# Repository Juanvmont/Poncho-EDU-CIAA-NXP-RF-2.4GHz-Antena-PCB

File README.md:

# Poncho-EDU-CIAA-NXP-RF-2.4GHz-Antena-PCB
Este circuito de poncho implementa una unidad de radio que opera en la banda de frecuencias abierta de 2.4GHz y compila con aplicaciones de la EDU-CIAA NXP que soportan el estándar IEEE 802.15.4: IEEE Standards Association. IEEE Standard for Local and metropolitan area networks–Part 15.4: Low-Rate Wireless Personal Area Networks (LR-WPANs) y ZIGBEE.

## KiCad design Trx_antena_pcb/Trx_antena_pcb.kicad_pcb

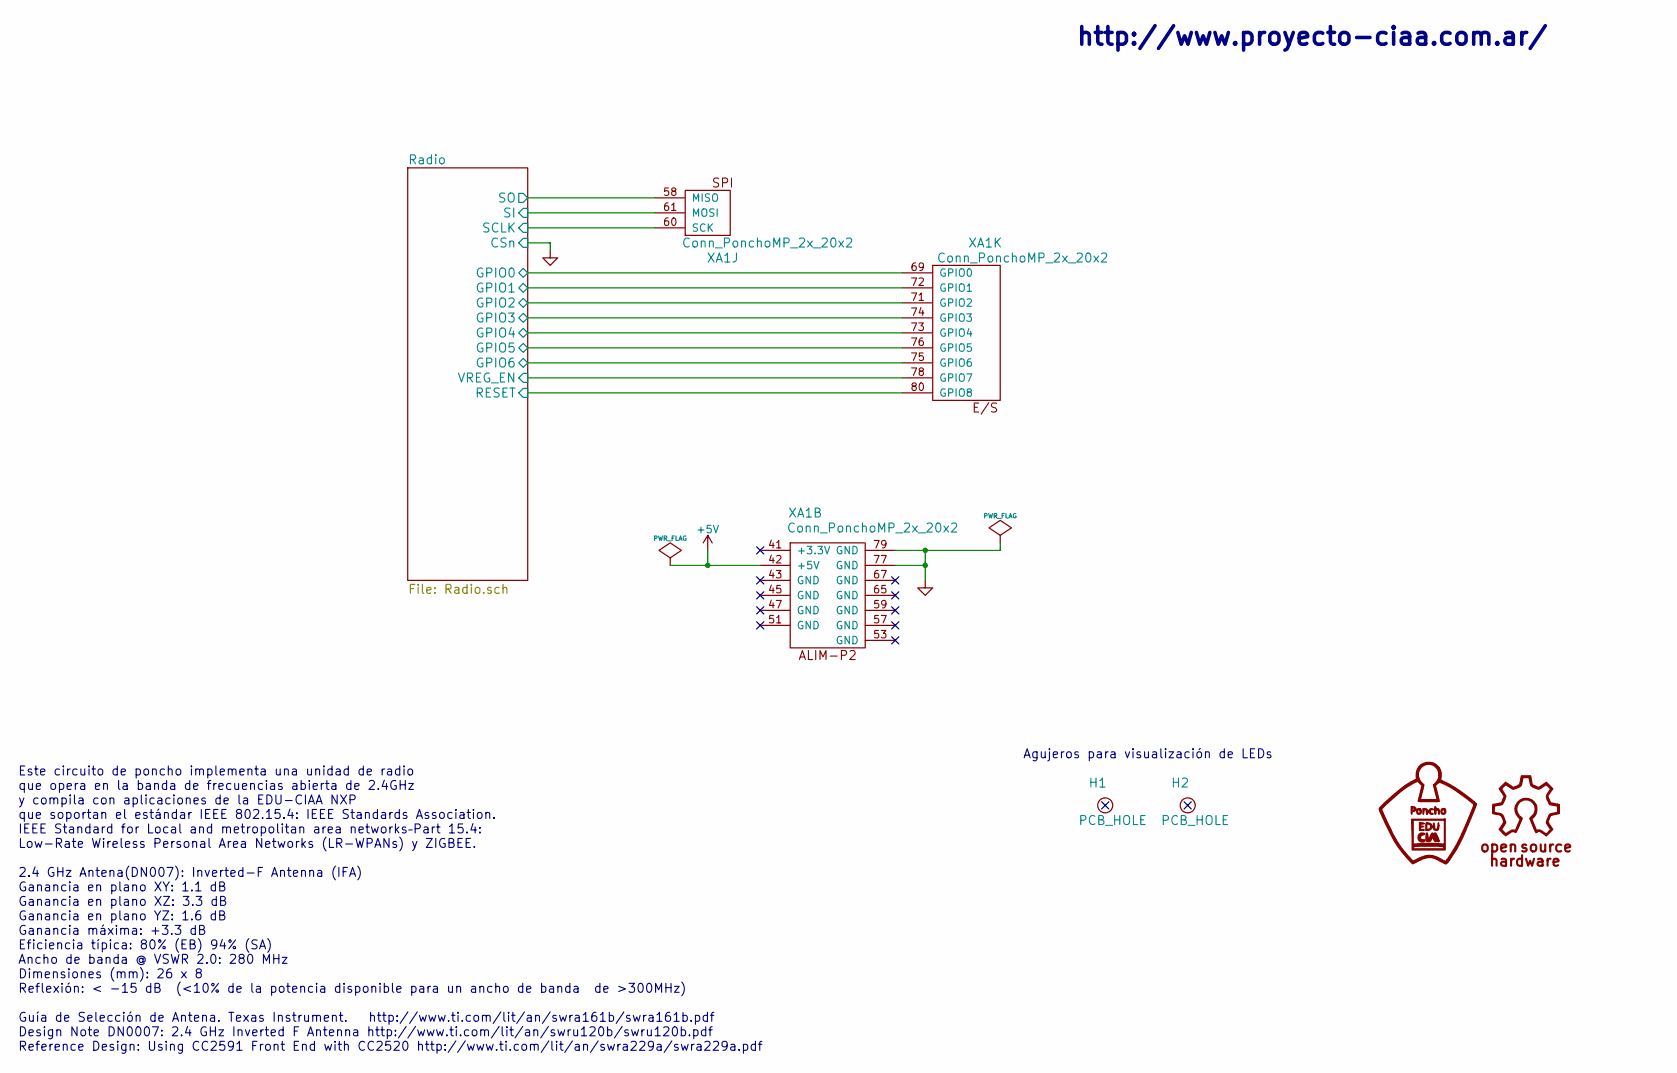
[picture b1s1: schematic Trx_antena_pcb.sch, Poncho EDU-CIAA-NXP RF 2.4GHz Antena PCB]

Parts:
H1, H2: PCB_HOLE; Led_Hole
XA1: Conn_PonchoMP_2x_20x2; Conn_Poncho_Izquierdo

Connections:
+5V: XA1.42 (+5V); also elsewhere on the board
/Radio/GPIO0: XA1.69 (GPIO0); also elsewhere on the board
/Radio/GPIO1: XA1.72 (GPIO1); also elsewhere on the board
/Radio/GPIO2: XA1.71 (GPIO2); also elsewhere on the board
/Radio/GPIO3: XA1.74 (GPIO3); also elsewhere on the board
/Radio/GPIO4: XA1.73 (GPIO4); also elsewhere on the board
/Radio/GPIO5: XA1.76 (GPIO5); also elsewhere on the board
/Radio/GPIO6: XA1.75 (GPIO6); also elsewhere on the board
/Radio/RESET: XA1.80 (GPIO8); also elsewhere on the board
/Radio/SCLK: XA1.60 (SCK); also elsewhere on the board
/Radio/SI: XA1.61 (MOSI); also elsewhere on the board
/Radio/SO: XA1.58 (MISO); also elsewhere on the board
/Radio/VREG_EN: XA1.78 (GPIO7); also elsewhere on the board
GND: XA1.77 (GND), XA1.79 (GND); also elsewhere on the board

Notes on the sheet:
http://www.proyecto-ciaa.com.ar/
Agujeros para visualización de LEDs
Este circuito de poncho implementa una unidad de radio que opera en la banda de frecuencias abierta de 2.4GHz y compila con aplicaciones de la EDU-CIAA NXP que soportan el estándar IEEE 802.15.4: IEEE Standards Association. IEEE Standard for Local and metropolitan area networks–Part 15.4: Low-Rate 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

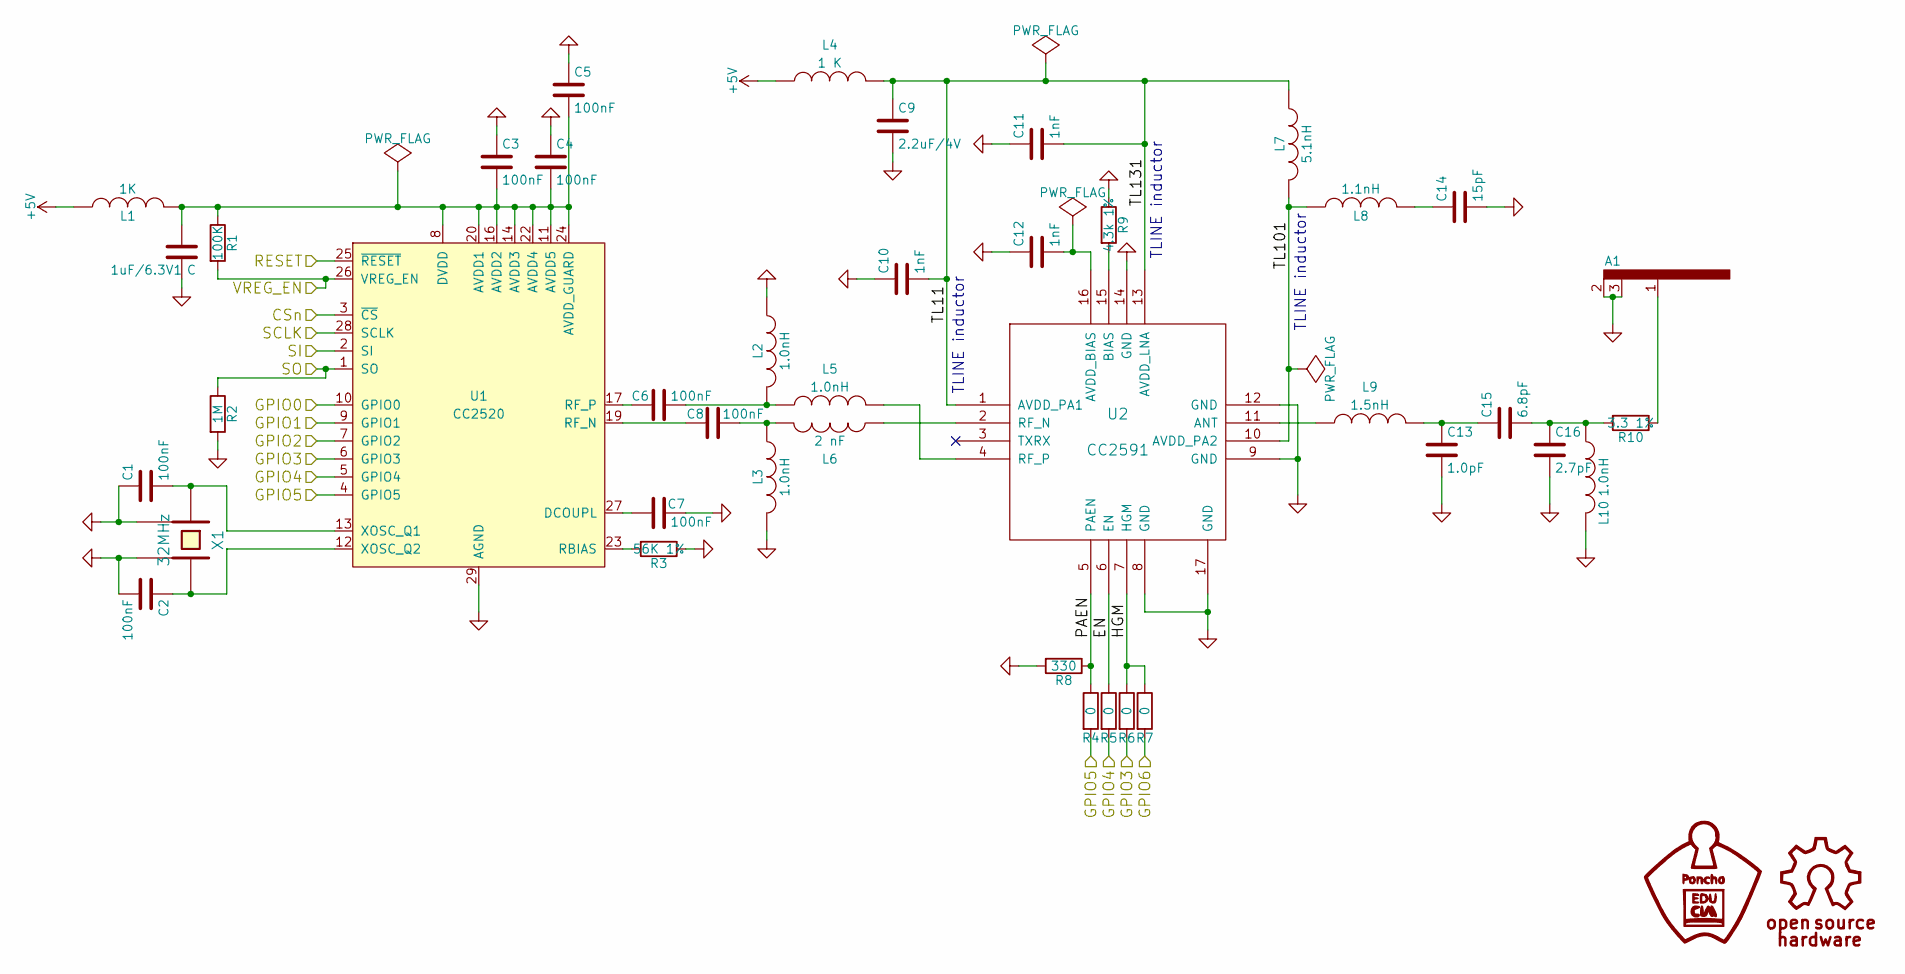
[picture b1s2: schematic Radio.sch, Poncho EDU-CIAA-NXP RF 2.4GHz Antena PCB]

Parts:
1uF/6.3V1: C; C_0402; Digikey# 490-3890-1-ND
A1: INV_F_ANT
C1, C2, C3, C4, C5, C6, C7, C8: 100nF; C_0402; Digikey# 311-1047-1-ND
C9: 2.2uF/4V; C_0402; Digikey# 445-3882-1-ND
C10, C11, C12: 1nF; C_0402; Digikey# 311-1036-1-ND
C13: 1.0pF; C_0402; Digikey# 490-3199-1-ND
C14: 15pF; C_0402; Digikey# 311-1017-1-ND
C15: 6.8pF; C_0402; Digikey# 490-5950-1-ND
C16: 2.7pF; C_0402; Digikey# 490-5934-1-ND
L1: 1K; C_0402; Digikey# 240-2555-1-ND
L2, L3, L5, L10: 1.0nH; C_0402; Digikey# 445-3035-1-ND
L4: 1 K; C_0402; Digikey# 240-2555-1-ND
L6: 2 nF; C_0402; Digikey# 445-3042-1-ND
L7: 5.1nH; C_0402; Digikey# 445-6360-1-ND
L8: 1.1nH; C_0402; Digikey# 445-6352-1-ND
L9: 1.5nH; C_0402; Digikey# 535-11505-1-ND
R1: 100K; R_0402; Digikey# RMCF0402JT1M00CT-ND
R2: 1M; R_0402; Digikey# RMCF0402JT1M00CT-ND
R3: 56K 1%; R_0402; Digikey# 311-56.0KLRCT-ND
R4, R5, R6, R7: 0; R_0402; Digikey# RMCF0402ZT0R00CT-ND
R8: 330; R_0402; Digikey# 311-330JRCT-ND
R9: 4.3k 1%; R_0402; Digikey# 311-4.30KLRCT-ND
R10: 3.3 1%; R_0402; Digikey# 311-3.30LRCT-ND
U1: CC2520; QFN-28-1EP_5x5mm_Pitch0.5mm; Digikey# 296-22996-1-ND
U2: CC2591; DFN-16-1EP_3x4mm_Pitch0.45mm; Digikey# 296-25327-1-ND
X1: 32MHz; Crystal_SMD_5032_4Pads; Digikey# 887-1312-1-ND

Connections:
+5V: L1.1, L4.1; also elsewhere on the board
/Radio/EN: R5.1, U2.6 (EN)
/Radio/GPIO0: U1.10 (GPIO0); also elsewhere on the board
/Radio/GPIO1: U1.9 (GPIO1); also elsewhere on the board
/Radio/GPIO2: U1.7 (GPIO2); also elsewhere on the board
/Radio/GPIO3: R6.2, U1.6 (GPIO3); also elsewhere on the board
/Radio/GPIO4: R5.2, U1.5 (GPIO4); also elsewhere on the board
/Radio/GPIO5: R4.2, U1.4 (GPIO5); also elsewhere on the board
/Radio/GPIO6: R7.2; also elsewhere on the board
/Radio/HGM: R6.1, R7.1, U2.7 (HGM)
/Radio/PAEN: R4.1, R8.1, U2.5 (PAEN)
/Radio/RESET: U1.25 (~RESET); also elsewhere on the board
/Radio/SCLK: U1.28 (SCLK); also elsewhere on the board
/Radio/SI: U1.2 (SI); also elsewhere on the board
/Radio/SO: R2.1, U1.1 (SO); also elsewhere on the board
/Radio/TL11: C9.1, C10.2, C11.2, L4.2, L7.1, U2.1 (AVDD_PA1), U2.13 (AVDD_LNA)
/Radio/TL101: L7.2, L8.1, U2.10 (AVDD_PA2)
/Radio/VREG_EN: R1.2, U1.26 (VREG_EN); also elsewhere on the board
GND: 1uF/6.3V1.2, A1.2, A1.3, C1.1, C2.2, C3.1, C4.1, C5.1, C7.2, C9.2, C10.1, C11.1, C12.1, C13.2, C14.2, C16.2, L2.1, L3.2, L10.2, R2.2, R3.1, R8.2, R9.1, U1.3 (~CS), U1.29 (AGND), U2.8 (GND), U2.9 (GND), U2.12 (GND), U2.14 (GND), U2.17 (GND), X1.2, X1.4; also elsewhere on the board
unnamed: 1uF/6.3V1.1, C3.2, C4.2, C5.2, L1.2, R1.1, U1.8 (DVDD), U1.11 (AVDD5), U1.14 (AVDD3), U1.16 (AVDD2), U1.20 (AVDD1), U1.22 (AVDD4), U1.24 (AVDD_GUARD)
unnamed: A1.1, R10.1
unnamed: C1.2, U1.13 (XOSC_Q1), X1.1
unnamed: C2.1, U1.12 (XOSC_Q2), X1.3
unnamed: C6.1, U1.17 (RF_P)
unnamed: C6.2, L2.2, L5.1
unnamed: C7.1, U1.27 (DCOUPL)
unnamed: C8.1, L3.1, L6.2
unnamed: C8.2, U1.19 (RF_N)
unnamed: C12.2, U2.16 (AVDD_BIAS)
unnamed: C13.1, C15.1, L9.2
unnamed: C14.1, L8.2
unnamed: C15.2, C16.1, L10.1, R10.2
unnamed: L5.2, U2.4 (RF_P)
unnamed: L6.1, U2.2 (RF_N)
unnamed: L9.1, U2.11 (ANT)
unnamed: R3.2, U1.23 (RBIAS)
unnamed: R9.2, U2.15 (BIAS)

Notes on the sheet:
TLINE inductor

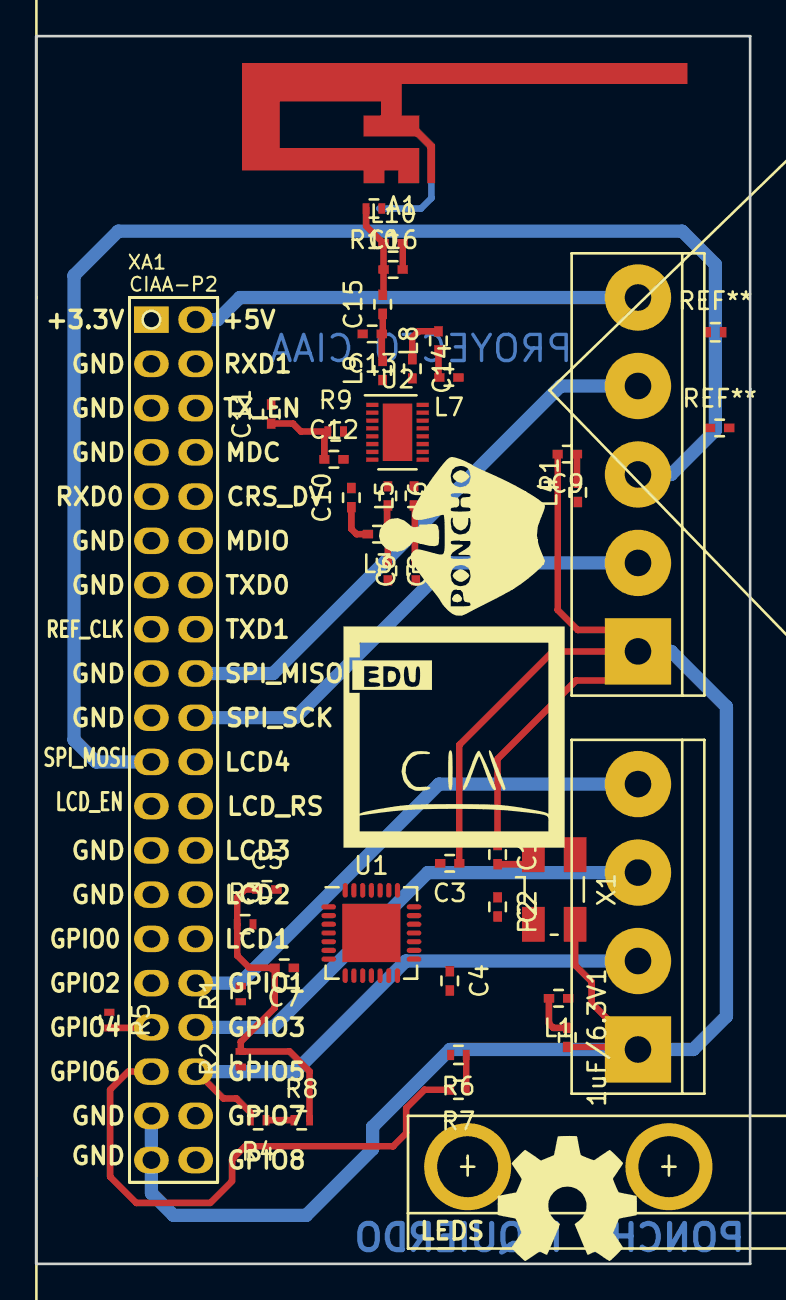
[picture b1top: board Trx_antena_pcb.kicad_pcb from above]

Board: 2 copper layers, 41.0 x 70.5 mm, 48 parts (0 on the bottom side), 37 nets.

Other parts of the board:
G101: Logo_OSHWA
MP1: Plantilla_EDU-CIAA
P1: CONN_5; bornier5
P2: CONN_4; bornier4

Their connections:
GND: P1.1, P2.1; also elsewhere on the board

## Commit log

2016-11-25 Adding the project and documentation
2016-11-25 actualizando el .odt del proyecto
2016-12-04 "Segundas correcciones. Documentacion"
2016-12-10 Completando esquematico de RF
2016-12-12 mattching pin tou from edu ciaa to poncho
2016-12-13 completando el esquematico
2016-12-21 cuarta correccion: revision2 en /doc
2016-12-24 layout de componentes en pcbnew
